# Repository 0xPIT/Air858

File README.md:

# Air858

Simplified and optimized replacement controller for 
the low-cost W.E.P. 858D+ Hot Air Soldering Station.

## Warning

**This project operates with possibly lethal mains voltage. If you are unsure what to do, don't do it and get help from an experienced tinkerer with professional training.**

## Image of PCB rev. 1
![BoardAllRev1]

Licensing
====================
```
The MIT License (MIT)

Copyright (c) 2016 karl@pitrich.com
All rights reserved.

Permission is hereby granted, free of charge, to any person obtaining a copy
of this software and associated documentation files (the "Software"), to deal
in the Software without restriction, including without limitation the rights
to use, copy, modify, merge, publish, distribute, sublicense, and/or sell
copies of the Software, and to permit persons to whom the Software is
furnished to do so, subject to the following conditions:

The above copyright notice and this permission notice shall be included in
all copies or substantial portions of the Software.

THE SOFTWARE IS PROVIDED "AS IS", WITHOUT WARRANTY OF ANY KIND, EXPRESS OR
IMPLIED, INCLUDING BUT NOT LIMITED TO THE WARRANTIES OF MERCHANTABILITY,
FITNESS FOR A PARTICULAR PURPOSE AND NONINFRINGEMENT. IN NO EVENT SHALL THE
AUTHORS OR COPYRIGHT HOLDERS BE LIABLE FOR ANY CLAIM, DAMAGES OR OTHER
LIABILITY, WHETHER IN AN ACTION OF CONTRACT, TORT OR OTHERWISE, ARISING FROM,
OUT OF OR IN CONNECTION WITH THE SOFTWARE OR THE USE OR OTHER DEALINGS IN
THE SOFTWARE.
```

[BoardAllRev1]:https://raw.githubusercontent.com/0xPIT/Air858/master/hardware/manufacturing/revisions/1/Air858.all.rev1.png

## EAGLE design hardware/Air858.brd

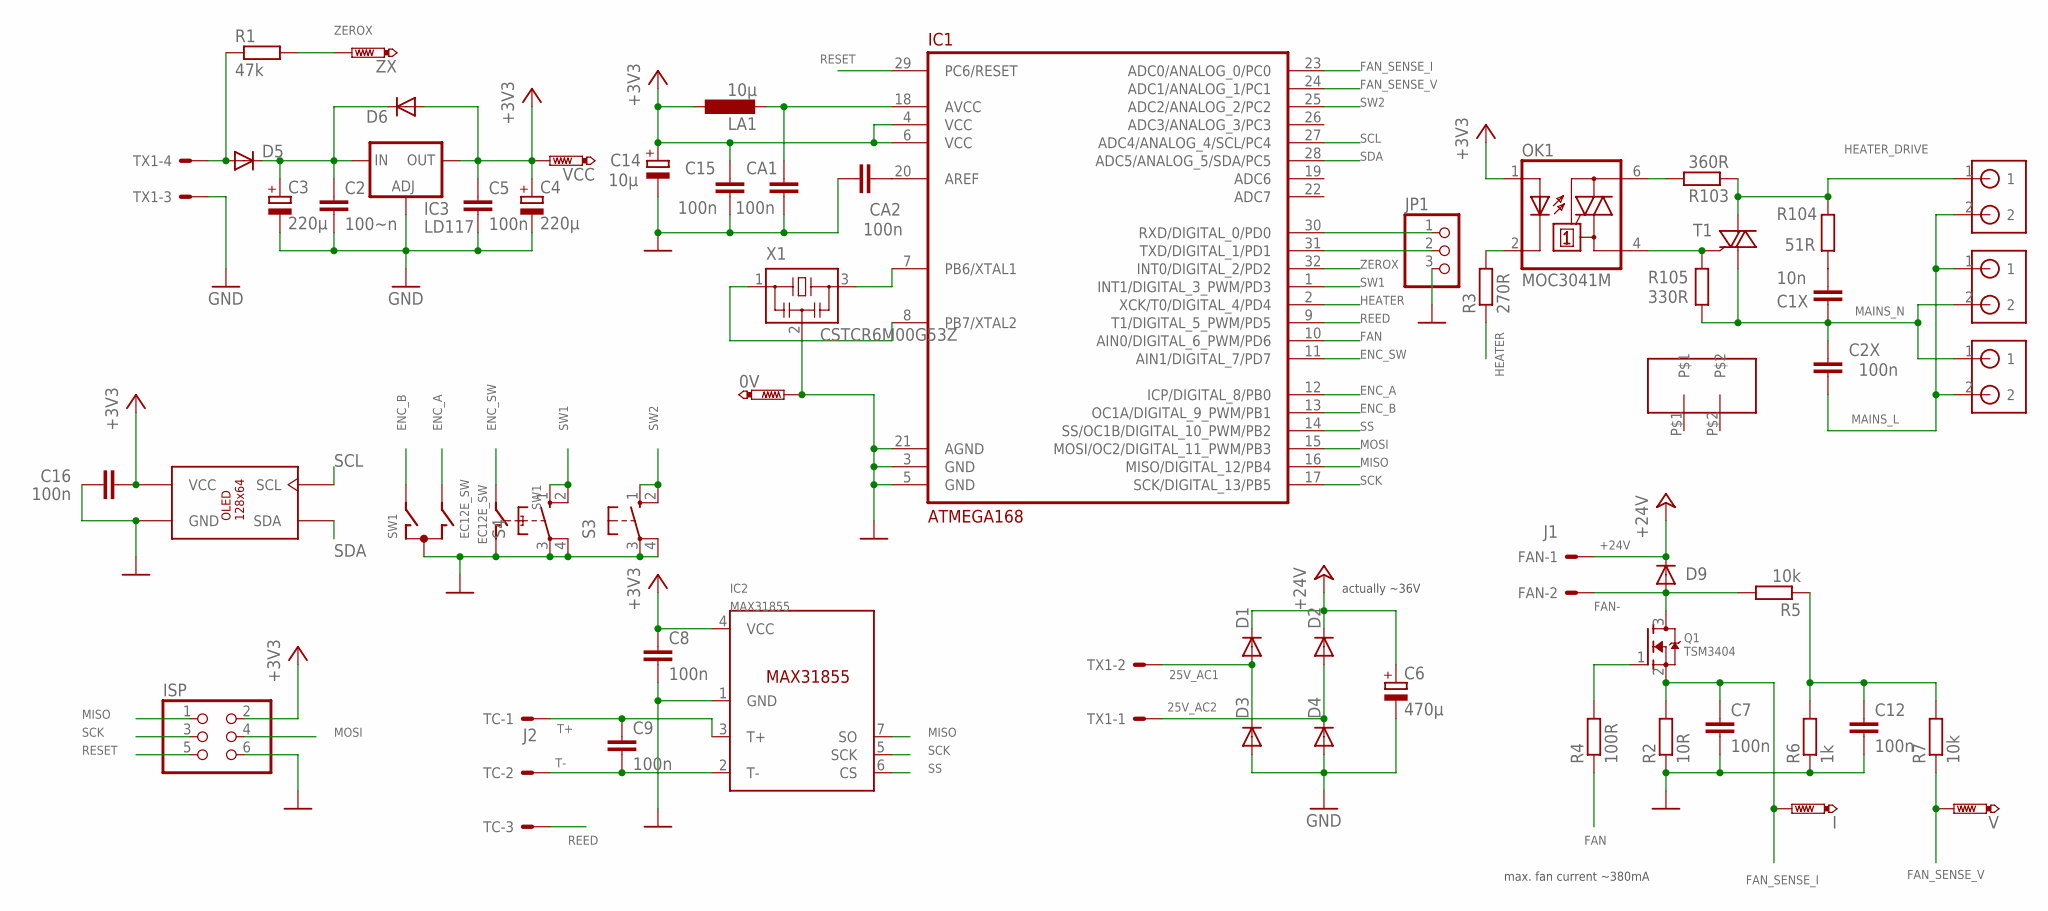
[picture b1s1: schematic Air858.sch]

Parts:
0V: PTR1B1,27; B1,27
C1X: 10n; C075-032X103
C2: 100~n; C0603
C2X: 100n; C150-054X183
C3, C4: 220µ; SMC_E
C5: 100n; C0603
C6: 470µ; E5-10,5
C7, C8, C9, C12, C15, C16: 100n; C0603K
C14: 10µ; B/3528-21W
CA1, CA2: 100n; C0603K
D1, D2, D3, D4, D5, D6, D9: DIODE-DO-214AC; DO-214AC
FAN: J1; 22-23-2021
HEATER: 2POL5MM
I: PTR1B1,27; B1,27
IC1: ATMEGA168; QFP32
IC2: MAX31855; SOIC8
IC3: LD117; SOT223
ISP: PINHD-2X3; 2X03
JP1: PINHD-1X3; 1X03
LA1: 10µ; L3225P
MAINS1, MAINS2: 2POL5MM
OK1: MOC3041M; DIL06
OLED1: SSD1306-IIC
Q1: TSM3404; SOT23
R1: 47k; R0603
R2: 10R; M1206
R3: 270R; R0603
R4: 100R; R0603
R5, R7: 10k; R0603
R6: 1k; R0603
R103: 360R; M1206
R104: 51R; 0309/10
R105: 330R; M1206
S3, S4: 40-XX; B3F-40XX
SW1: EC12E_SW; ALPS_EC12E_SW
T1: BTA16; TO220BV
TC: J2; 22-23-2031
TX1: J4; 22-23-2041
U$5: HEATSINK17X7.5TO220
V: PTR1B1,27; B1,27
VCC: PTR1B1,27; B1,27
X1: CSTCR6M00G53Z; CSTCR6M
ZX: PTR1B1,27; B1,27

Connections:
10V_AC1: D5.A, R1.1, TX1.4
25V_AC1: D1.A, D3.C, TX1.2
25V_AC2: D2.A, D4.C, TX1.1
+3V3: C4.+, C5.1, C8.1, C14.+, C15.1, C16.2, D6.A, IC1.4 (VCC), IC1.6 (VCC), IC2.4 (VCC), IC3.4 (OUT), ISP.2, LA1.1, OK1.1 (A), OLED1.VCC, VCC.TP
+24V: C6.+, D1.C, D2.C, D9.C, FAN.1
AREF: CA2.2, IC1.20 (AREF)
AVCC: CA1.1, IC1.18 (AVCC), LA1.2
ENC_A: IC1.12 (ICP/DIGITAL_8/PB0), SW1.B
ENC_B: IC1.13 (OC1A/DIGITAL_9_PWM/PB1), SW1.A
ENC_SW: IC1.11 (AIN1/DIGITAL_7/PD7), SW1.E (2)
FAN: IC1.10 (AIN0/DIGITAL_6_PWM/PD6), R4.1
FAN-: D9.A, FAN.2, Q1.3 (D), R5.2
FAN_SENSE_I: C7.1, I.TP, IC1.23 (ADC0/ANALOG_0/PC0), Q1.2 (S), R2.2
FAN_SENSE_V: IC1.24 (ADC1/ANALOG_1/PC1), R7.1, V.TP
GND: 0V.TP, C2.2, C3.-, C4.-, C5.2, C6.-, C7.2, C8.2, C12.2, C14.-, C15.2, C16.1, CA1.2, CA2.1, D3.A, D4.A, IC1.3 (GND), IC1.5 (GND), IC1.21 (AGND), IC2.1 (GND), IC3.1 (ADJ), ISP.6, JP1.3, OLED1.GND, R2.1, R6.1, S3.3, S3.4 (P1), S4.3, S4.4 (P1), SW1.C, SW1.D (1), TX1.3, X1.2
HEATER: IC1.2 (XCK/T0/DIGITAL_4/PD4), R3.1
HEATER_DRIVE: HEATER.1, R103.1, R104.2, T1.T2 (A2)
MAINS_L: C2X.1, HEATER.2, MAINS1.1, MAINS2.2
MAINS_N: C1X.1, C2X.2, MAINS1.2, MAINS2.1, R105.2, T1.T1 (A1)
MISO: IC1.16 (MISO/DIGITAL_12/PB4), IC2.7 (SO), ISP.1
MOSI: IC1.15 (MOSI/OC2/DIGITAL_11_PWM/PB3), ISP.4
unnamed: C12.1, R5.1, R6.2, R7.2
unnamed: OK1.6 (A2), R103.2
unnamed: C2.1, C3.+, D5.C, D6.C, IC3.3 (IN)
unnamed: OK1.2 (C), R3.2
unnamed: OK1.4 (A1), R105.1, T1.G
unnamed: C1X.2, R104.1
unnamed: IC1.7 (PB6/XTAL1), X1.3
unnamed: Q1.1 (G), R4.2
unnamed: IC1.8 (PB7/XTAL2), X1.1
REED: IC1.9 (T1/DIGITAL_5_PWM/PD5), TC.3
RESET: IC1.29 (PC6/RESET), ISP.5
RXD: IC1.30 (RXD/DIGITAL_0/PD0), JP1.1
SCK: IC1.17 (SCK/DIGITAL_13/PB5), IC2.5 (SCK), ISP.3
SCL: IC1.27 (ADC4/ANALOG_4/SCL/PC4), OLED1.SCL
SDA: IC1.28 (ADC5/ANALOG_5/SDA/PC5), OLED1.SDA
SS: IC1.14 (SS/OC1B/DIGITAL_10_PWM/PB2), IC2.6 (CS)
SW1: IC1.1 (INT1/DIGITAL_3_PWM/PD3), S4.1 (S), S4.2 (S1)
SW2: IC1.25 (ADC2/ANALOG_2/PC2), S3.1 (S), S3.2 (S1)
T+: C9.1, IC2.3 (T+), TC.1
T-: C9.2, IC2.2 (T-), TC.2
TXD: IC1.31 (TXD/DIGITAL_1/PD1), JP1.2
ZEROX: IC1.32 (INT0/DIGITAL_2/PD2), R1.2, ZX.TP

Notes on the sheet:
max. fan current ~380mA
actually ~36V

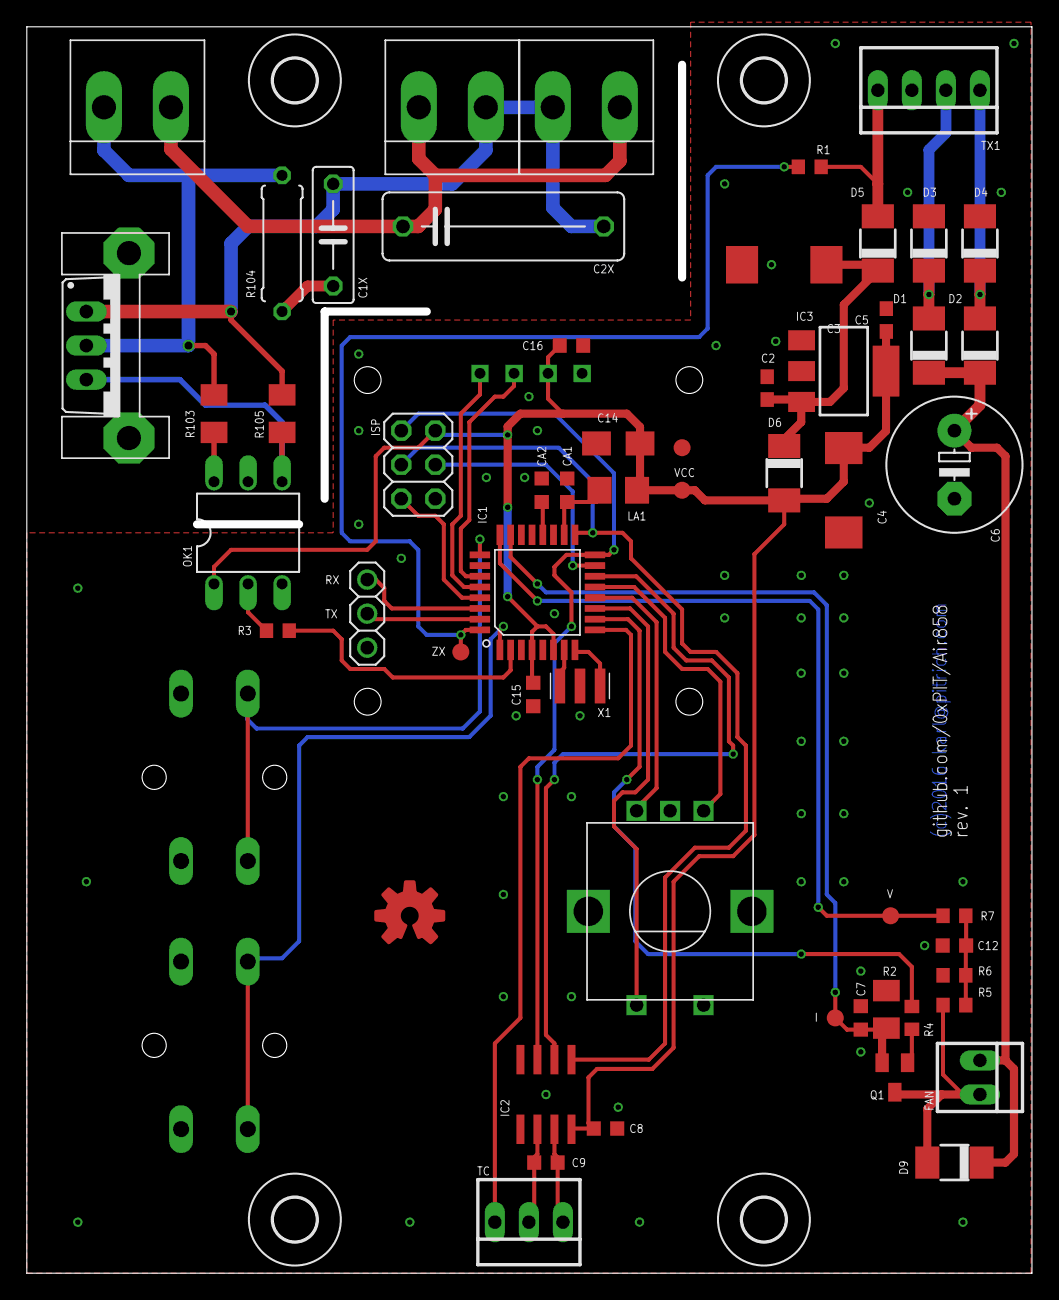
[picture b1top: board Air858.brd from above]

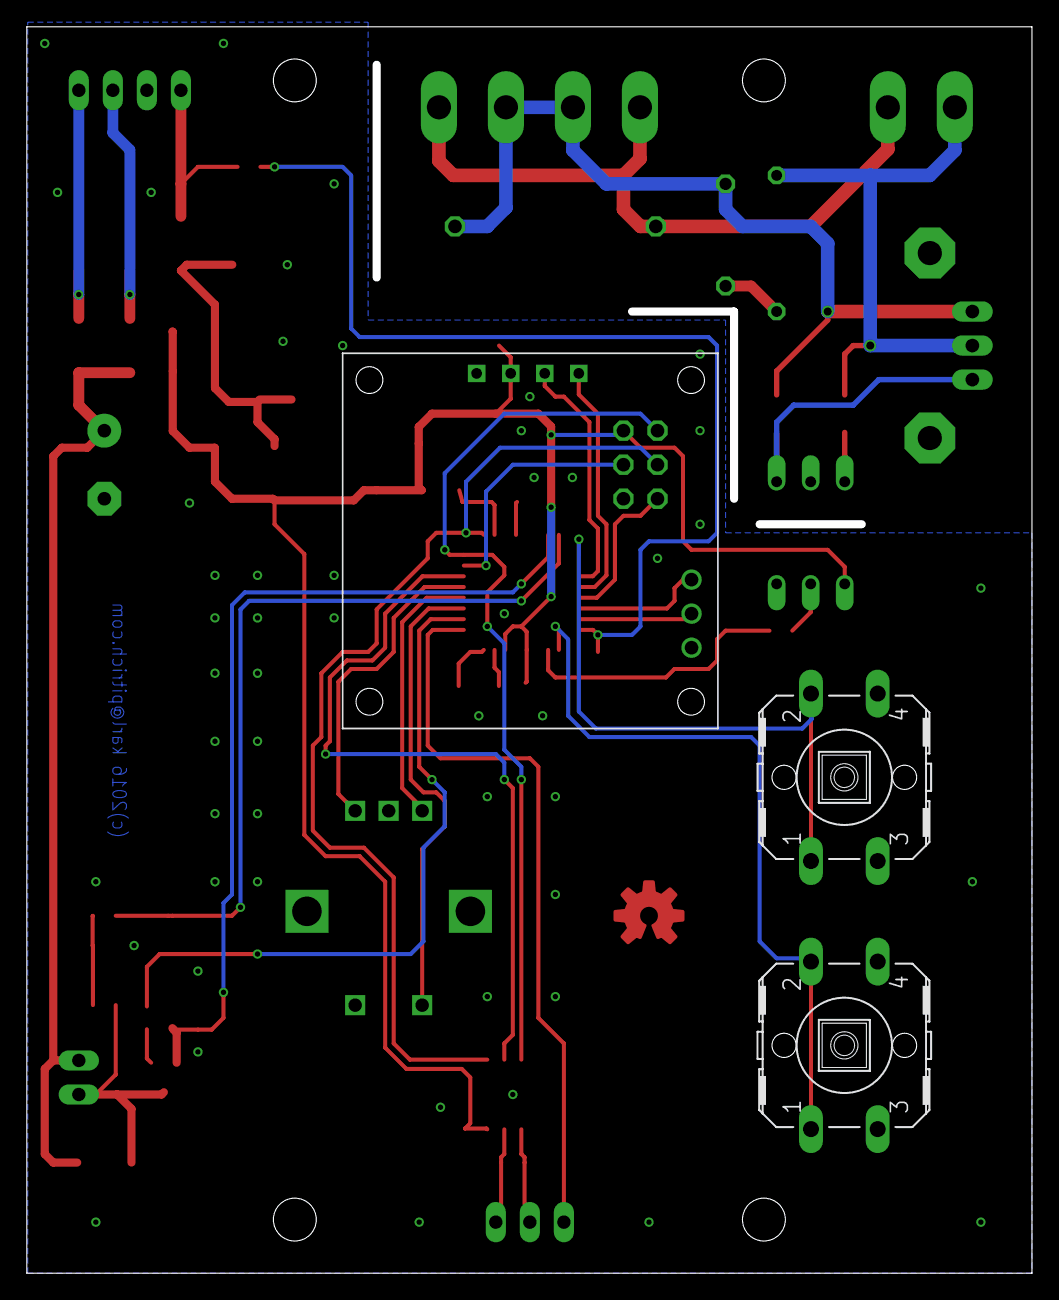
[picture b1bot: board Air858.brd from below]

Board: 2 copper layers, 74.4 x 92.4 mm, 64 parts (3 on the bottom side), 43 nets.

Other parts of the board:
U$1, U$2, U$3, U$4: 3,2
U$6: OSHWLOGO_TOP_0.2

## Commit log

2016-10-31 add gitignore
2016-10-31 initial push of rev.1 pcb
2016-10-31 add manufacturing files
2016-11-01 changed zero crossing detection based on AVR182
2016-11-01 update license & readme
2016-11-02 fix schematic issues and update board
2016-11-12 rev 1: prototype
2016-11-12 add board file to rev1 zip
2016-11-12 add board picture
2016-11-12 add warning
2016-11-12 add oshw logo
